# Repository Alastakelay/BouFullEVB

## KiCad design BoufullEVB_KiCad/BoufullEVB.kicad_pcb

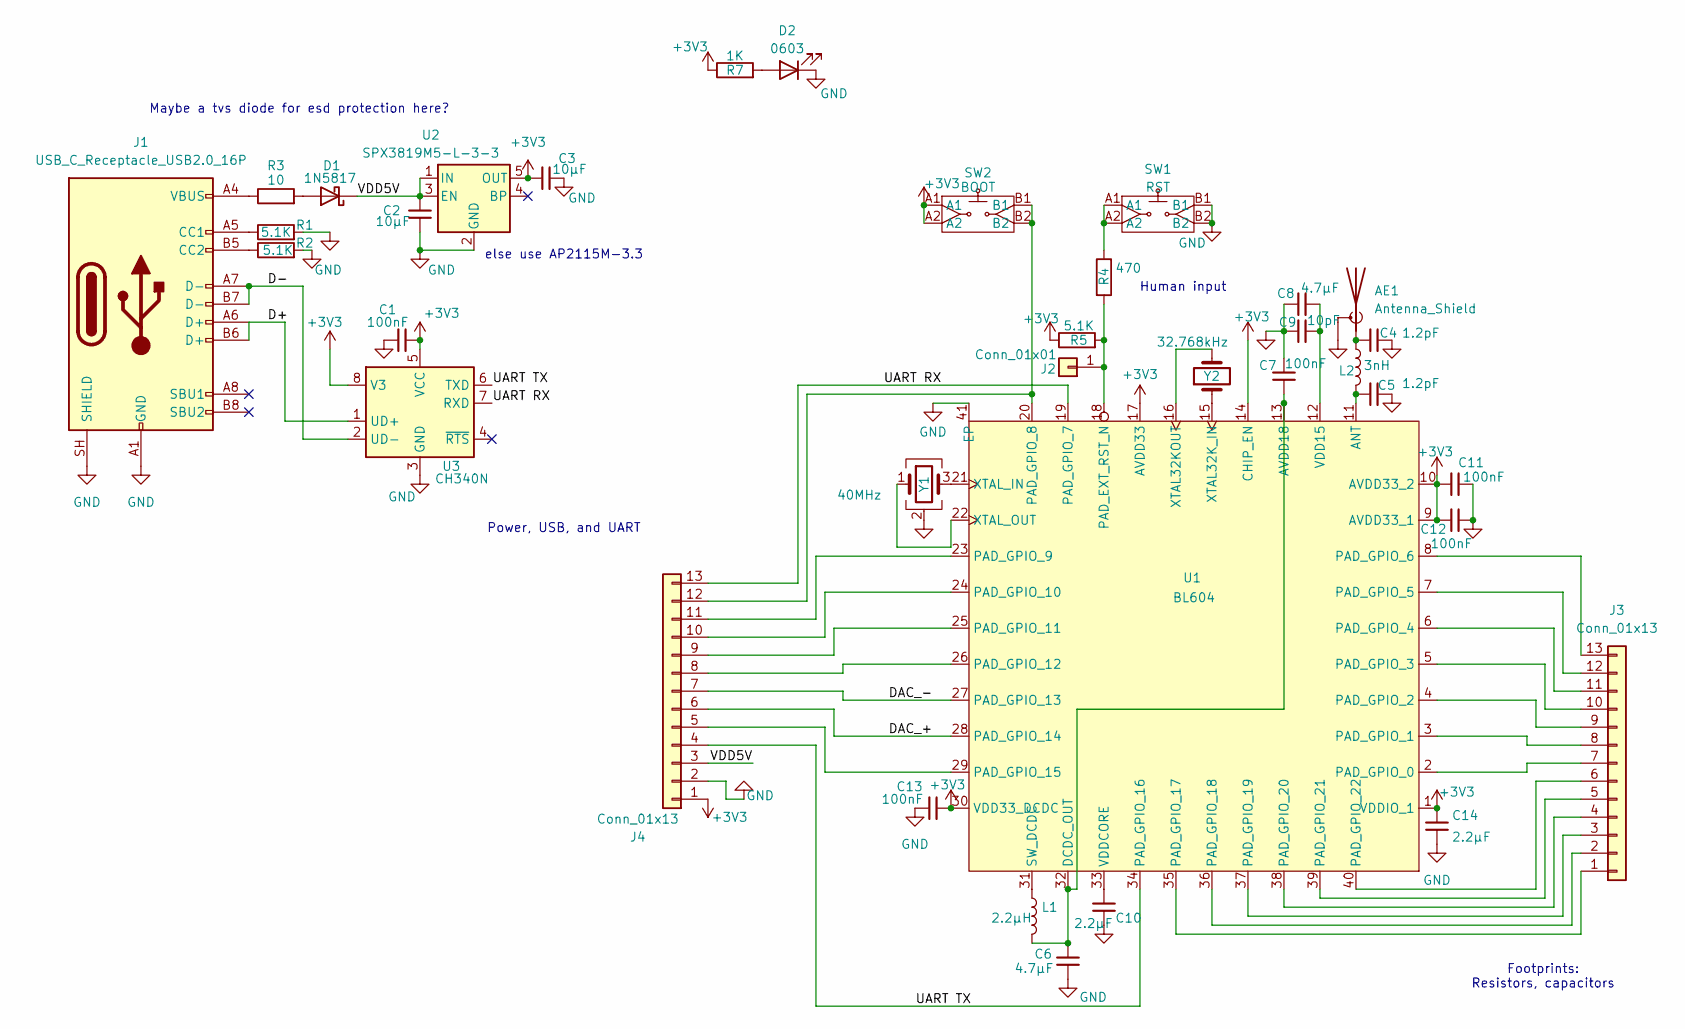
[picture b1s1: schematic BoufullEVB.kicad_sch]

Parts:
AE1: Antenna_Shield; Texas_SWRA117D_2.4GHz_Right
C1, C7, C11, C12, C13: 100nF; C_0603_1608Metric
C2, C3: 10µF; C_0603_1608Metric
C4, C5: 1.2pF; C_0603_1608Metric
C6: 4.7μF; C_0603_1608Metric
C8: 4.7µF; C_0603_1608Metric
C9: 10pF; C_0603_1608Metric
C10, C14: 2.2μF; C_0603_1608Metric
D1: 1N5817; D_SOD-123
D2: 0603; LED_0603_1608Metric
J1: USB_C_Receptacle_USB2.0_16P; USB_C_Receptacle_GCT_USB4105-xx-A_16P_TopMnt_Horizontal
J2: Conn_01x01; PinHeader_1x01_P2.54mm_Vertical
J3, J4: Conn_01x13; PinHeader_1x13_P2.54mm_Vertical
L1: 2.2μH; L_1008_2520Metric
L2: 3nH; L_0603_1608Metric
R1, R2, R5: 5.1K; R_0603_1608Metric
R3: 10; R_0603_1608Metric
R4: 470; R_0603_1608Metric
R7: 1K; R_0603_1608Metric
SW1: RST; R-667842
SW2: BOOT; R-667842
U1: BL604; QFN-40-1EP_5x5mm_P0.4mm_EP3.6x3.6mm
U2: SPX3819M5-L-3-3; SOT-23-5
U3: CH340N; JEITA_SOIC-8_3.9x4.9mm_P1.27mm
Y1: 40MHz; Crystal_SMD_ECS-4Pin_2.0x1.6mm
Y2: 32.768kHz; Crystal_SMD_Abracon_ABS07-2Pin_3.2x1.5mm

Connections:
+3V3: C1.2, C3.1, C11.1, C12.1, C13.2, C14.1, J4.1, R5.1, R7.1, SW2.A1, SW2.A2, U1.1 (VDDIO_1), U1.9 (AVDD33_1), U1.10 (AVDD33_2), U1.14 (CHIP_EN), U1.17 (AVDD33), U1.30 (VDD33_DCDC), U2.5 (OUT), U3.5 (VCC), U3.8 (V3)
/D+: J1.A6 (D+), J1.B6 (D+), U3.1 (UD+)
/D-: J1.A7 (D-), J1.B7 (D-), U3.2 (UD-)
/DAC_+: J4.6, U1.28 (PAD_GPIO_14)
/DAC_-: J4.7, U1.27 (PAD_GPIO_13)
/UART RX: J4.13, U1.19 (PAD_GPIO_7), U3.7 (RXD)
/UART TX: J4.4, U1.34 (PAD_GPIO_16), U3.6 (TXD)
/VDD5V: C2.1, D1.1 (K), J4.3, U2.1 (IN), U2.3 (EN)
GND: AE1.2 (Shield), C1.1, C2.2, C3.2, C4.2, C5.2, C6.2, C7.2, C8.1, C9.1, C10.1, C11.2, C12.2, C13.1, C14.2, D2.1 (K), J1.A1 (GND), J1.A12 (GND), J1.B1 (GND), J1.B12 (GND), J1.SH (SHIELD), J4.2, R1.2, R2.2, SW1.B1, SW1.B2, U1.41 (EP), U2.2 (GND), U3.3 (GND), Y1.2 (G), Y1.4 (G)
unnamed: AE1.1 (A_1), C4.1, L2.1
unnamed: D1.2 (A), R3.2
unnamed: D2.2 (A), R7.2
unnamed: J1.A5 (CC1), R1.1
unnamed: J1.B5 (CC2), R2.1
unnamed: J1.A4 (VBUS), J1.A9 (VBUS), J1.B4 (VBUS), J1.B9 (VBUS), R3.1
unnamed: J2.1 (Pin_1_1), R4.2, R5.2, U1.18 (PAD_EXT_RST_N)
unnamed: J3.1, U1.35 (PAD_GPIO_17)
unnamed: J3.2, U1.36 (PAD_GPIO_18)
unnamed: J3.3, U1.37 (PAD_GPIO_19)
unnamed: J3.4, U1.38 (PAD_GPIO_20)
unnamed: J3.5, U1.39 (PAD_GPIO_21)
unnamed: J3.6, U1.40 (PAD_GPIO_22)
unnamed: J3.7, U1.2 (PAD_GPIO_0)
unnamed: J3.8, U1.3 (PAD_GPIO_1)
unnamed: J3.9, U1.4 (PAD_GPIO_2)
unnamed: J3.10, U1.5 (PAD_GPIO_3)
unnamed: J3.11, U1.6 (PAD_GPIO_4)
unnamed: J3.12, U1.7 (PAD_GPIO_5)
unnamed: J3.13, U1.8 (PAD_GPIO_6)
unnamed: J4.5, U1.29 (PAD_GPIO_15)
unnamed: J4.8, U1.26 (PAD_GPIO_12)
unnamed: J4.9, U1.25 (PAD_GPIO_11)
unnamed: J4.10, U1.24 (PAD_GPIO_10)
unnamed: J4.11, U1.23 (PAD_GPIO_9)
unnamed: J4.12, SW2.B1, SW2.B2, U1.20 (PAD_GPIO_8)
unnamed: R4.1, SW1.A1, SW1.A2
unnamed: C5.1, L2.2, U1.11 (ANT)
unnamed: C6.1, C7.1, L1.2, U1.13 (AVDD18), U1.32 (DCDC_OUT)
unnamed: L1.1, U1.31 (SW_DCDC)
unnamed: C8.2, C9.2, U1.12 (VDD15)
unnamed: C10.2, U1.33 (VDDCORE)
unnamed: U1.16 (XTAL32KOUT), Y2.2
unnamed: U1.15 (XTAL32K_IN), Y2.1
unnamed: U1.21 (XTAL_IN), Y1.3
unnamed: U1.22 (XTAL_OUT), Y1.1

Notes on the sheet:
Maybe a tvs diode for esd protection here?
Footprints: Resistors, capacitors
Power, USB, and UART
else use AP2115M-3.3
Human input

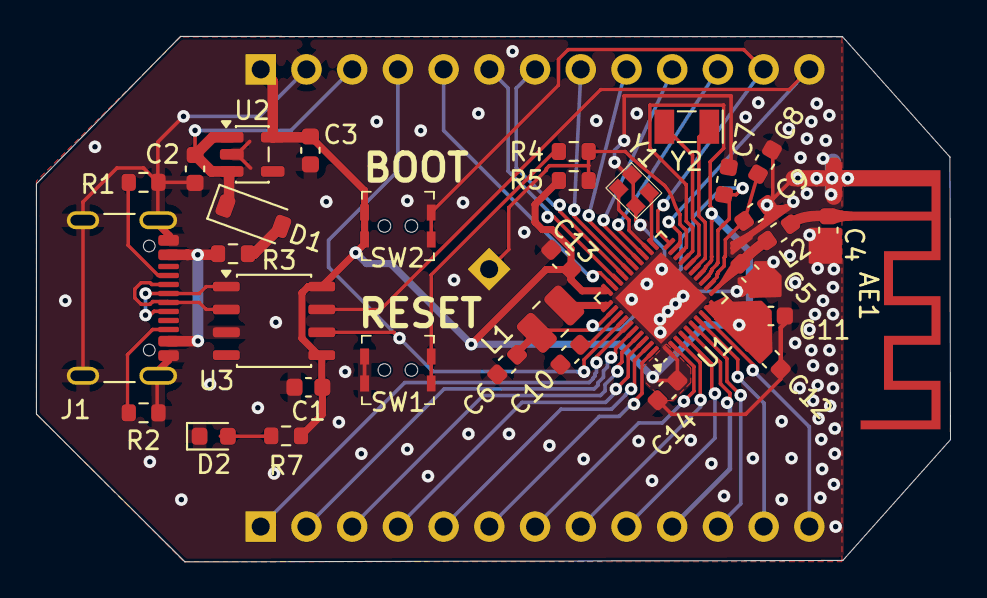
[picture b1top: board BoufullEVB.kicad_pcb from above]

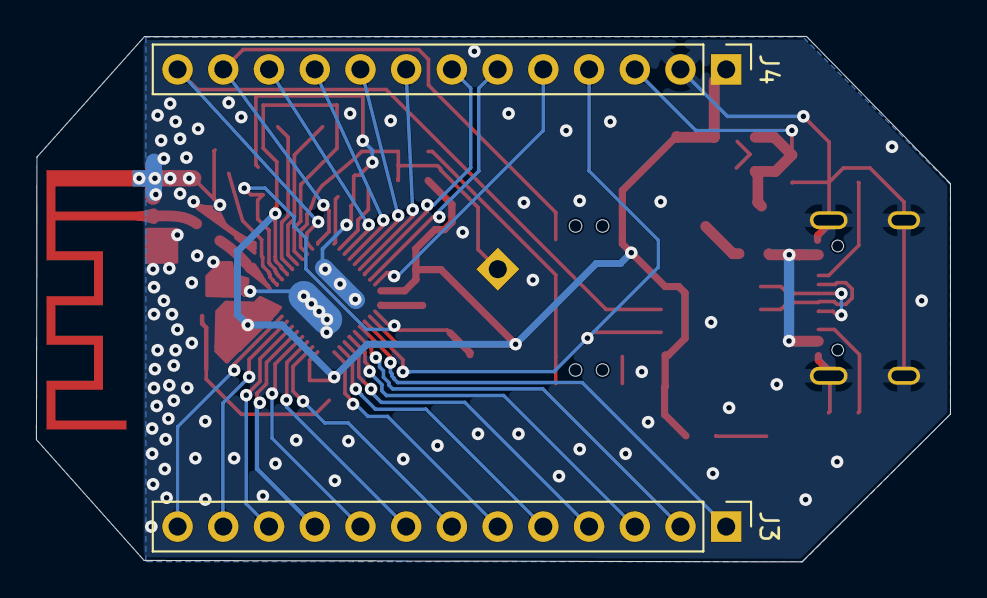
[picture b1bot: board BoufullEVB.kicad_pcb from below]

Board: 2 copper layers, 50.8 x 29.2 mm, 36 parts (2 on the bottom side), 45 nets.
